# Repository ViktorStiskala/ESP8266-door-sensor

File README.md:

# ESP8266 low power door sensor

This design represents a small sensor intended to be triggered by a magnetic reed switch. It wakes upon closing the contact, reporting the information to the internet and going back to sleep. All while retaining minimum power consumption.

## PCB design

- [Schematic design](pcb/schematic/Door.pdf)
- [Gerblook](http://gerblook.org/pcb/wmdqLb5envAoFVmN6yVcNm)

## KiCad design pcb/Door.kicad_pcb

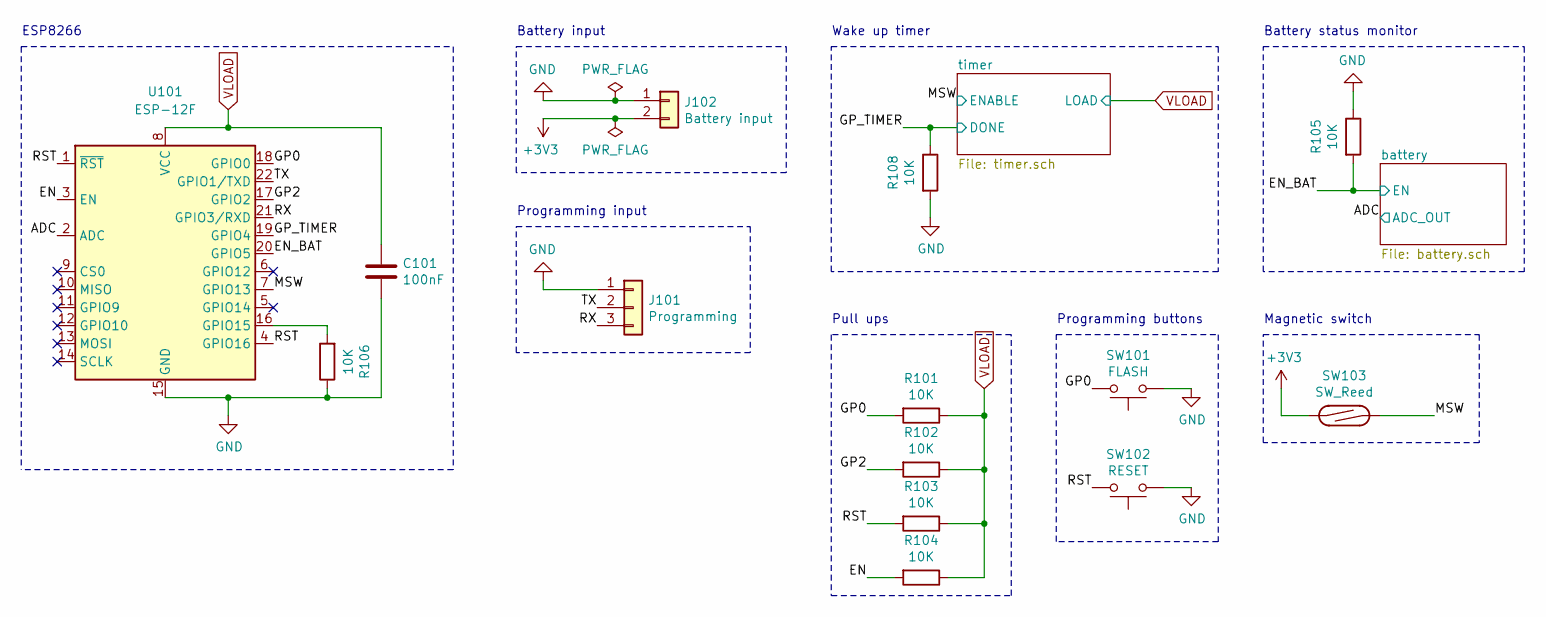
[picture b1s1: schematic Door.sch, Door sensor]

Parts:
C101: 100nF; C_0805_2012Metric
J101: Programming; PinHeader_1x03_P2.54mm_Vertical
J102: Battery input; PH_MPT_0,5_2-2,54
R101, R102, R103, R104, R105, R106, R108: 10K; R_0805_2012Metric
SW101: FLASH; SW_SPST_B3U-1000P
SW102: RESET; SW_SPST_B3U-1000P
SW103: SW_Reed; PH_MPT_0,5_2-2,54
U101: ESP-12F; ESP-12E

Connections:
+3V3: J102.2, SW103.2; also elsewhere on the board
/ADC: U101.2 (ADC); also elsewhere on the board
/EN: R104.2, U101.3 (EN)
/EN_BAT: R105.2, U101.20 (GPIO5); also elsewhere on the board
/GP0: R101.2, SW101.2, U101.18 (GPIO0)
/GP2: R102.2, U101.17 (GPIO2)
/GP_TIMER: R108.1, U101.19 (GPIO4); also elsewhere on the board
/MSW: SW103.1, U101.7 (GPIO13); also elsewhere on the board
/RST: R103.2, SW102.2, U101.1 (~RST), U101.4 (GPIO16)
/RX: J101.3, U101.21 (GPIO3/RXD)
/TX: J101.2, U101.22 (GPIO1/TXD)
GND: C101.2, J101.1, J102.1, R105.1, R106.1, R108.2, SW101.1, SW102.1, U101.15 (GND); also elsewhere on the board
unnamed: R106.2, U101.16 (GPIO15)
VLOAD: C101.1, R101.1, R102.1, R103.1, R104.1, U101.8 (VCC); also elsewhere on the board

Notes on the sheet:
Pull ups
Battery input
Programming input
Battery status monitor
Wake up timer
ESP8266
Programming buttons
Magnetic switch

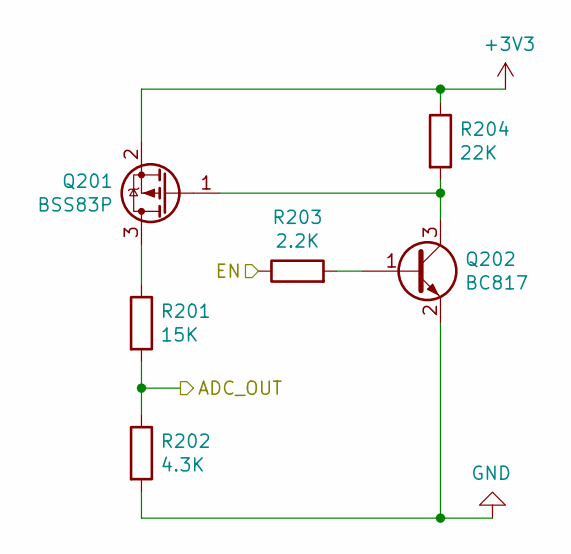
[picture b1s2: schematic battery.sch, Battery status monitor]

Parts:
Q201: BSS83P; SOT-23
Q202: BC817; SOT-23
R201: 15K; R_0805_2012Metric
R202: 4.3K; R_0805_2012Metric
R203: 2.2K; R_0805_2012Metric
R204: 22K; R_0805_2012Metric

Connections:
+3V3: Q201.2 (S), R204.1; also elsewhere on the board
/ADC: R201.2, R202.1; also elsewhere on the board
/EN_BAT: R203.1; also elsewhere on the board
GND: Q202.2 (E), R202.2; also elsewhere on the board
unnamed: Q201.1 (G), Q202.3 (C), R204.2
unnamed: Q201.3 (D), R201.1
unnamed: Q202.1 (B), R203.2

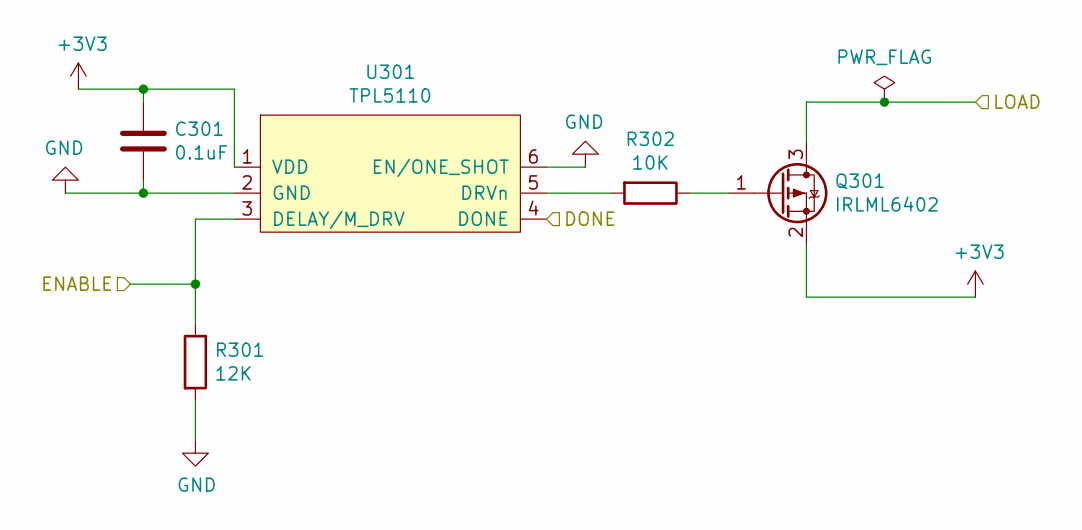
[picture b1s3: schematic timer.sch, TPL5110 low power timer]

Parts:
C301: 0.1uF; C_0805_2012Metric
Q301: IRLML6402; SOT-23
R301: 12K; R_0805_2012Metric
R302: 10K; R_0805_2012Metric
U301: TPL5110; SOT-23-6

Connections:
+3V3: C301.1, Q301.2 (S), U301.1 (VDD); also elsewhere on the board
/GP_TIMER: U301.4 (DONE); also elsewhere on the board
/MSW: R301.1, U301.3 (DELAY/M_DRV); also elsewhere on the board
GND: C301.2, R301.2, U301.2 (GND), U301.6 (EN/ONE_SHOT); also elsewhere on the board
unnamed: Q301.1 (G), R302.1
unnamed: R302.2, U301.5 (DRVn)
VLOAD: Q301.3 (D); also elsewhere on the board

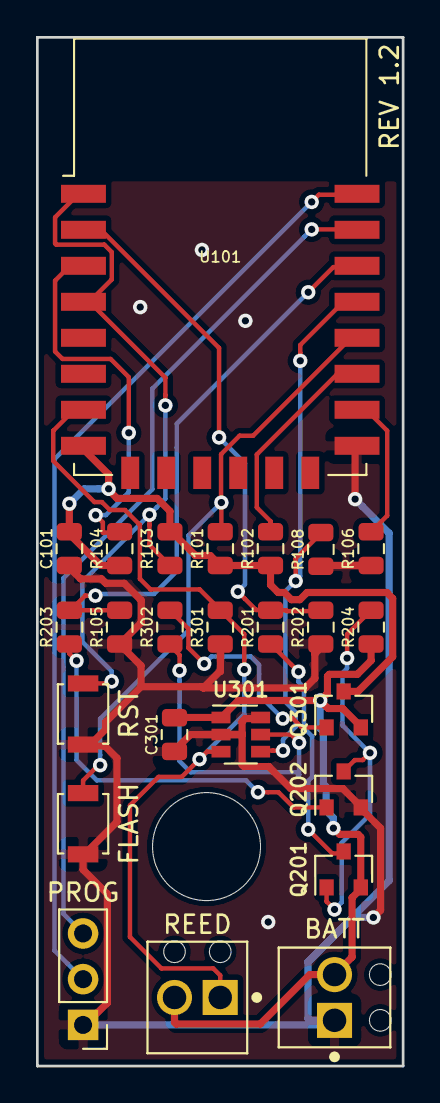
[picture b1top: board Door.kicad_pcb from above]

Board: 2 copper layers, 20.3 x 57.1 mm, 25 parts (0 on the bottom side), 19 nets.

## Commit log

2019-04-28 Revision 1.2
2019-04-28 Changed directory structure
2019-04-28 Hole clearance update
